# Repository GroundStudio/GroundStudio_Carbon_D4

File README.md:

GroundStudio Carbon D4
====================================

Get it from [ardushop.ro](https://ardushop.ro/en/electronics/1186-placa-de-dezvoltare-carbon-d4-6427854000408.html)

Explore all the GroundStudio products at [ardushop.ro](https://ardushop.ro/en/37-groundstudio)

Description
-------------------
Features ESP32 based Pico D4 SiP with 2.4GHz Wifi, V4.2 Bluetooth, 8MB external SPI PSRAM, 520kB internal SRAM, 448kB ROM, 14 GPIO, 8 ADC and 6 touch sensitive pins, I²C 3V3 adapter, RGB smart LED, 1 cell LiPo/LiIon battery charger with optional battery connector and CH340C for USB comunication.

Contents
-------------------

* [/Documentation](https://github.com/GroundStudio/GroundStudio_Carbon_D4/tree/main/Documentation) -- Pinout.
* [/Hardware](https://github.com/GroundStudio/GroundStudio_Carbon_D4/tree/main/Hardware) -- Schematics, layout.

Versions
-------------------
*(Not all tags shown)*

* [REV0.0.2]
  * added testpoint for GPIO0
  * R16 and R17 connected in series
  * interchanged GPIO2 and GPIO12 functions because GPIO12 cannot be pulled high while in flash mode
  * added 100nF in parallel with R13 for better battery voltage level reading
  * adjusted the pin labels for better visibility

License
-------------------

This is released under the [Attribution-ShareAlike 4.0 International (CC BY-SA 4.0)](https://creativecommons.org/licenses/by-sa/4.0/) license. 
**You are welcome to use this for commercial purposes.**

Please consider contributing back to this project or others to help the open-source hardware community continue to thrive and grow! 

Certifications:

[Open Source Hardware Association](https://certification.oshwa.org/ro000006.html)   
   
[
](https://certification.oshwa.org/ro000006.html)

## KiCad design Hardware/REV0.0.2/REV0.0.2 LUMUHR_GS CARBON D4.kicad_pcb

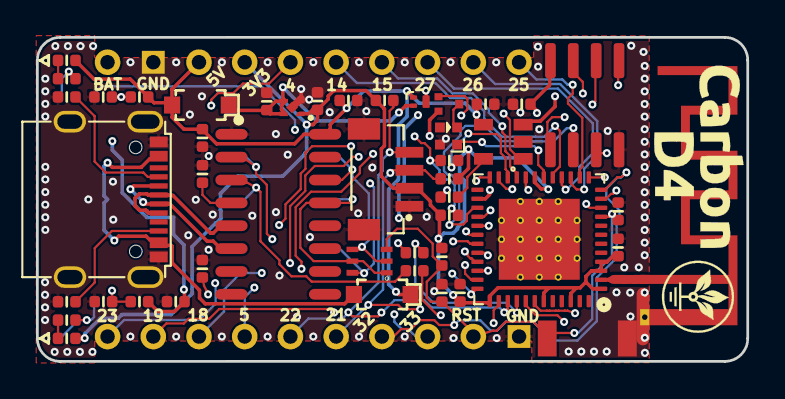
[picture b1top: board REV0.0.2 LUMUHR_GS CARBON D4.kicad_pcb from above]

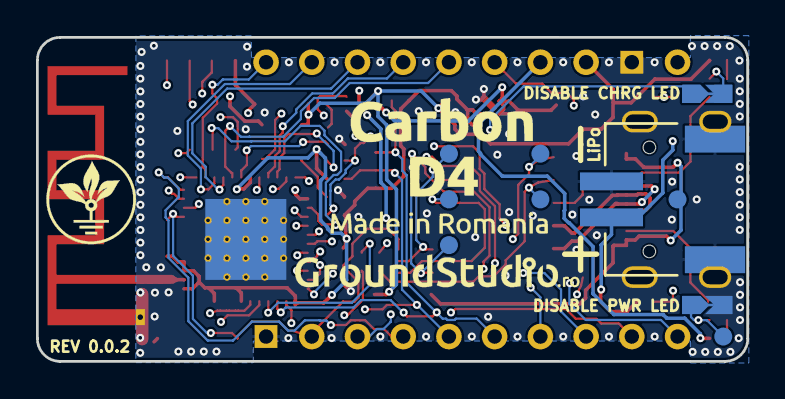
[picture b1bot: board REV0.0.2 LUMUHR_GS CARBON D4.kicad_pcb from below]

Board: 4 copper layers, 39.5 x 18.0 mm, 58 parts (5 on the bottom side), 53 nets.

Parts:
A1: SWRA117D_2.4GHz; Texas_SWRA117D_2.4GHz_Left
C1, C2, C3, C7, C8: C_0402_1uF_10V; C_0402_alt
C4, C5, C11, C12: C_0402_100nF_16V; C_0402_alt
C6, C9: C_0402_10uF_10V; C_0402_alt
C10: C_0402_10nF_50V; C_0402_alt
CR1: SOD-123 B0520LW; SOD-123
D1: SOD-123 B0520LW; SOD-123
D2: LED_0402_GREEN; LED_0402_alt
IC1: SOIC-8_3.9x4.9 LY68L6400SLIT; SOIC-8_3.9x4.9mm_P1.27mm
IC2: SOT23-5 BRCL4054CME; SOT-23-5
J1, J2: PinHeader_1x10_P2.54_V_M C57369; PinHeader_1x10_P2.54mm_Vertical_Male
J3: disable CHARGING LED; SolderJumper_NC
J4: PWR LED DISABLE; SolderJumper_NC
LED1: SK6805-EC15 DY-S1515065; SK6805-EC15
LED2: LED_0402_RED; LED_0402_alt
Q1: SOT-363 MUN5214DW1T1G; SOT-363
Q2: SOT-883 LP0404N3T5G; SOT-883
R1, R2, R3, R14: R_0402_3.3k; R_0402_alt
R4: R_0402_alt 0402WGJ0103TCE; R_0402_alt
R5, R9: R_0402_2k; R_0402_alt
R6, R7: R_0402_5.1k; R_0402_alt
R8: R_0402_820k; R_0402_alt
R10: R_0402_100k; R_0402_alt
R11: R_0402_442k; R_0402_alt
R12, R15, R16, R17: R_0402_1k; R_0402_alt
R13: R_0402_160k; R_0402_alt
REG1: FBP1-1-4_ME6211C33U4AG-N; FBP1-1-4
SW1: TS342A2P-WZ
T1: SOT-723_DTA143ZMT2L; SOT-723
TP1: TP_USB_VCC; TestPoint
TP2: TP_DTR; TestPoint
TP3: TP_TX; TestPoint
TP4: TP_RTS; TestPoint
TP5: TP_ONL; TestPoint
TP6: TP_RX; TestPoint
TP7: IO0; TestPoint
U1: QFN-48-7x7 ESP32-D4; QFN-48-1EP_7x7mm_P0.5mm_EP4.5x4.5mm
U2: SOP-16_150MIL CH340C; SOP-16_150MIL
USB1: USB_C_C167321 C167321; USB_C_C167321
X1: SH__1x04_Vertical C145961; SH__1x04_P1.00mm_Vertical
X2: PH__1x02_P2.00mm_Horizontal C47647; PH__1x02_P2.00mm_Horizontal

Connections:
+3V3: C3.1, C5.1, C6.1, J1.4, LED2.2, R1.2, R2.1, R4.2, R8.1, REG1.1, T1.2, U1.1, U1.3, U1.4, U1.19, U1.37, U1.43, U1.46, X1.2
+BAT: C9.1, IC2.3, J1.1, Q2.3, R11.2, X2.2
CH340C_RX: R16.1, TP6.~, U2.3
CH340C_TX: R17.1, TP3.~, U2.2
CLK: IC1.6, U1.31
D+: U2.5, USB1.A6, USB1.B6
D-: U2.6, USB1.A7, USB1.B7
DTR: Q1.1, Q1.5, TP2.~, U2.13
EN: C1.1, C7.1, J2.9, Q1.3, R4.1, SW1.2, U1.9
Feed: A1.1, U1.2
GND: A1.2, C1.2, C2.1, C3.2, C4.2, C5.2, C6.2, C7.2, C8.2, C9.2, C10.1, C11.2, C12.2, IC1.4, IC2.2, J1.2, J2.10, J4.2, LED1.4, R5.1, R6.2, R7.2, R10.1, R13.1, R14.1, REG1.2, REG1.5, SW1.1, U1.49, U2.1, USB1.0, USB1.A1, USB1.A12, USB1.B1, USB1.B12, X1.0, X1.1, X2.0, X2.1
GPIO0: Q1.6, TP7.~, U1.23
GPIO2: R9.2, U1.22
GPIO4: J1.5, U1.24
GPIO5: J2.4, U1.34
GPIO7: IC1.3, U1.32
GPIO8: IC1.5, U1.33
GPIO9: R3.1, R5.2, U1.28
GPIO10: IC1.1, U1.29
GPIO11: IC1.7, U1.30
GPIO12: LED1.1, U1.18
GPIO13: T1.1, U1.20
GPIO14: J1.6, U1.17
GPIO15: J1.7, U1.21
GPIO17: IC1.2, U1.27
GPIO18: J2.3, U1.35
GPIO19: J2.2, U1.38
GPIO21: J2.6, R1.1, U1.42, X1.3
GPIO22: J2.5, R2.2, U1.39, X1.4
GPIO23: J2.1, U1.36
GPIO25: J1.10, U1.14
GPIO26: J1.9, U1.15
GPIO27: J1.8, U1.16
GPIO32: J2.7, U1.12
GPIO33: J2.8, U1.13
unnamed: C10.2, U2.4
unnamed: D2.1, R12.2
unnamed: IC2.5, R14.2
unnamed: J3.2, R12.1
unnamed: J4.1, R15.2, TP5.~
unnamed: LED1.2, T1.3
unnamed: LED2.1, R15.1
unnamed: R6.1, USB1.B5
unnamed: R7.1, USB1.A5
RTS: Q1.2, Q1.4, TP4.~, U2.14
RX_ESP32: R17.2, U1.40
TX_ESP32: R16.2, U1.41
USB: C8.1, C11.1, CR1.2, D1.1, D2.2, IC2.4, J1.3, Q2.1, R3.2, R10.2, U2.16
VBUS: C2.2, CR1.1, Q2.2, REG1.3, REG1.4
VBUS1*2: D1.2, TP1.~, USB1.A4, USB1.A9, USB1.B4, USB1.B9
VDDSDIO: C4.1, IC1.8, U1.26
VDET_2: C12.1, R11.1, R13.2, U1.11
~CHRG: IC2.1, J3.1, R8.2, R9.1, U1.10

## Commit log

2022-08-08 - initial commit
2022-08-16 - added "Kicad6" to revision folder name
2022-08-26 - added schematic pdf file
2022-12-06 - added "Arduino" folder for code examples
2022-12-06 - added "CarbonD4_neopixel_test" Arduino example
2023-03-15 Update README.md
    - removed references to "library"
2023-10-25 - added datasheet
2023-10-26 - added .step 3D file of the board
2023-12-07 - updated pinout and datasheet to REV 1.1
2024-07-08 - fixed pins order in spiSD.begin
2025-09-10 update shop links
